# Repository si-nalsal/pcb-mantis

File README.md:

# SvayamV3_IIK — STM32H743 Flight Controller

**6-layer · 125 × 90 mm · STM32H743IIK6 · 16 servo channels · 9 protected peripheral ports**

> ### ⚠️ Design status: layout in progress — **not fabrication-ready**
> Schematic is complete and frozen (ERC **0 errors**). Placement is finalised and **every
> functional net is electrically connected** (`unconnected_items` = 0), but DRC still reports
> **2 shorts** — both vias sitting inside one unassigned connector `MP` pad — plus vias and
> drills outside the current rule set. **Do not order boards from this revision.**
> See [docs/STATUS.md](docs/STATUS.md).

---

## Contents

| | |
|---|---|
| [What this is](#what-this-is) | [Board specifications](#board-specifications) |
| [Hardware architecture](#hardware-architecture) | [Repository layout](#repository-layout) |
| [Documentation](#documentation) | [Opening the project](#opening-the-project) |
| [Board statistics](#board-statistics) | [Fabrication](#fabrication) |
| [Open items before fabrication](#open-items-before-fabrication) | [License](#license) |

---

## What this is

A servo-based UAV flight controller built around the **STM32H743IIK6** (Cortex-M7,
UFBGA-201, 0.65 mm pitch). The board distributes power to a fixed-wing/multirotor airframe
with **16 PWM servo outputs**, redundant IMU and barometer sensing, dual CAN, USB-C, micro-SD
logging, and nine current-limited peripheral ports for GPS, telemetry radios, and external
sensors.

Design priorities, in order:

1. **Repairability** — silkscreen carries *function* labels (`Channel 1`…`Channel 16`,
   `TELEM1`, `GPS`, `SBUS`, …) instead of values; component values live on the `F.Fab`
   layer so they stay readable in the editor and in fab documentation without cluttering
   the assembled board.
2. **Survivability** — every external port sits behind a TPS2553 current limiter; TVS
   diodes on the battery and servo rails; separate LDO domains for FMU and sensors.
3. **Do-no-harm to the airframe** — the `+VSERVO` rail is *fail-last*: it has no on-board
   source and no series fuse, so a failed BEC cannot brown out the flight controller.

---

## Board specifications

| Parameter | Value | Source |
|---|---|---|
| Board size | 125.15 × 89.96 mm (11,258 mm²) | `kicad-cli pcb export stats` |
| Layers | 6 — `F.Cu` / `In1.Cu` / `In2.Cu` / `In3.Cu` / `In4.Cu` / `B.Cu` | board setup |
| Finished thickness | 1.5584 mm | board setup |
| Copper weight | 1 oz outer (35 µm), 0.5 oz inner (15.2 µm) | board setup |
| Target stackup | JLCPCB `JLC06161H-3313` (3313 / FR4 / 2116 prepregs) | [docs/STACKUP.md](docs/STACKUP.md) |
| Surface finish | ENIG | board setup |
| MCU | STM32H743IIK6 — UFBGA-201, 10 × 10 mm, 0.65 mm pitch | `U1` |
| HSE crystal | 8 MHz, SMD5032-2P | `Y1` (X50328MSB2GI) |
| Minimum track width | 0.10 mm (BGA fan-out only) | DRC report |
| Minimum drill | 0.15 mm (BGA fan-out vias) | DRC report |
| Vias | 475 through-hole (0.30 / 0.20 / 0.15 mm drill) | board stats |
| Pads | 1,005 SMD · 63 THT · 6 NPTH | board stats |
| Component placements | 290 (190 front / 100 back) | board stats |
| Design rules | `SvayamV3_IIK.kicad_dru` — global 0.127 mm, BGA rule area, net classes | project |

---

## Hardware architecture

### Compute and storage

| Ref | Part | Function |
|---|---|---|
| `U1` | STM32H743IIK6 | Cortex-M7 FMU, 480 MHz |
| `U2` | FM25CL64B | 64 kbit FRAM for parameters (SPI) |
| `J10` | Molex 104031-0811 | micro-SD card, card-detect |
| `J7` | 1×05 2.54 mm | SWD / debug service header |
| `Y1` | X50328MSB2GI | 8 MHz HSE crystal (`U1` PH0/PH1) |

### Sensing — redundant by design

| Ref | Part | Function |
|---|---|---|
| `U7` | BMI088 | IMU #1 (accel + gyro) |
| `U8` | BMI270 | IMU #2 |
| `U5` | BMP388 | barometer #1 |
| `U6` | DPS310XTSA1 | barometer #2 |
| `U9` | BMM150 | magnetometer (WLCSP-12) |

The sensor block is laid out as its own quiet zone with a dedicated `+3V3_SENS` domain and
local copper pour, kept away from the switching regulator.

### Power chain

```
POWER1 (J9) ─┐
             ├─► U10 TPS2120  power mux ─► U11 TPS63070  buck-boost 5 V ─► U14 AP22804 ─► +5V_PERIPH
POWER2 (J16)─┘        (ILIM R24 = 33k)          (R27/R28 → 4.99 V)                        │
                                                                                          ├─► U16…U24  9× TPS2553 current limiters
                                                                                          │     GPS · TELEM1 · TELEM2 · SERIAL4 ·
                                                                                          │     SERIAL5 · I2C · CAN · CAN2 · SPI
                                              U12 RT9080 ─► +3V3_FMU  (MCU, IO)            │
                                              U13 RT9080 ─► +3V3_SENS (sensor zone)        │
                                              U15 USBLC6-2SC6 ─► USB-C ESD              +VSERVO
                                                                                          (external BEC, fail-last)
```

* TVS: `D4`/`D5` on `+VBRICK1`/`+VBRICK2`, `D8` SMAJ6.0A on `+VSERVO`.
* `+VSERVO` reservoir: `C78` 220 µF bulk + 16 × 1 µF per channel.
* Per-port trip current is set by each limiter's `RILIM`: `U16` R84 33k, `U17` R85 33k,
  `U18` R86 75k, `U19` R87 75k, `U20` R88 110k, `U21` R89 47k, `U22` R90 56k,
  `U23` R91 110k, `U24` R92 47k.

### Connectors

| Purpose | Ref | Purpose | Ref |
|---|---|---|---|
| POWER1 | `J9` | POWER2 | `J16` |
| RCIN / SBUS | `J6` | GPS | `J2` |
| TELEM1 | `J4` | TELEM2 | `J5` |
| SERIAL4 | `J8` | SERIAL5 | `J14` |
| I2C | `J17` | SPI | `J3` |
| CAN | `J13` | CAN2 | `J18` |
| SAFETY | `J15` | BUZZER | `J11` |
| ADC | `J12` | SD card | `J10` |
| USB-C | `J1` | SWD service | `J7` |

Servo outputs `J19`–`J34` (JST-XH `B3B-XH-A`, 2.50 mm, pin order **S / V+ / GND**) map
`Channel 1`…`Channel 16` in physical order along the board edge.

---

## Repository layout

```
.
├── SvayamV3_IIK.kicad_pro      # KiCad 10 project
├── SvayamV3_IIK.kicad_sch      # root sheet
│   ├── microcontroller.kicad_sch
│   ├── sensor.kicad_sch
│   ├── power.kicad_sch
│   └── connector.kicad_sch
├── SvayamV3_IIK.kicad_pcb      # 6-layer board
├── SvayamV3_IIK.kicad_dru      # custom DRC rules (global + BGA rule area)
├── fp-lib-table                # project footprint table (${KIPRJMOD})
├── sym-lib-table               # project symbol table (${KIPRJMOD})
├── Library/                    # custom + converted libraries (symbols, footprints, 3D)
├── docs/
│   ├── schematic.pdf           # full multi-sheet schematic (exported)
│   ├── STATUS.md               # live status + open DRC items
│   ├── DESIGN.md               # design decisions and their rationale
│   ├── STACKUP.md              # layer stackup and impedance notes
│   ├── board-stats.txt         # kicad-cli board statistics
│   ├── bom.csv                 # BOM (grouped by value + footprint)
│   ├── images/                 # PCB previews for this README
│   └── reports/                # dated ERC / DRC reports
└── fabrication/
    └── README.md               # fab gate, export commands, JLCPCB notes
```

Machine-local working files (`.history/`, `output/`, `*-backups/`, `*.kicad_prl`,
`.deepseek-sources/`) are deliberately **not** tracked — see `.gitignore`.

---

## Documentation

| Document | What it answers |
|---|---|
| [docs/STATUS.md](docs/STATUS.md) | Where the design is right now; open DRC items; next steps |
| [docs/DESIGN.md](docs/DESIGN.md) | Why the power chain, limiter setpoints and sensor redundancy look like this |
| [docs/STACKUP.md](docs/STACKUP.md) | Layer order, dielectrics, trace width / current table, via classes |
| [docs/schematic.pdf](docs/schematic.pdf) | Printable schematic, all four sheets |
| [docs/bom.csv](docs/bom.csv) | BOM — 88 line items (49 still need an MPN) |
| [docs/reports/](docs/reports/) | Raw `kicad-cli` ERC and DRC output, dated |
| [fabrication/README.md](fabrication/README.md) | What must pass before gerbers may be exported |

---

## Opening the project

1. KiCad **10.0** or newer (`generator_version 10.0`, format `20260206`). Older KiCad
   cannot open the project.
2. Open `SvayamV3_IIK.kicad_pro`. Both library tables resolve through `${KIPRJMOD}`, so the
   project is self-contained — no global library setup required.
3. Run **Tools → Update PCB from Schematic (F8)** only if the PCB and schematic have drifted;
   on a clean checkout they are in parity (0 issues).

> **Known limitation:** `sym-lib-table` registers the custom library under the nickname
> `Svayam_Symbol`, while the schematic references it as `Svayam`, and a stale `tps63070`
> entry points at a footprint directory. Symbols are embedded in the sheets, so the project
> opens and plots correctly — but ERC will report 9 `lib_symbol_issues` warnings until the
> table nickname is aligned. See [docs/STATUS.md](docs/STATUS.md#known-library-table-issues).

---

## Board statistics

Numbers below come straight from `kicad-cli pcb export stats` and the ERC/DRC reports in
[docs/reports/](docs/reports/):

| Metric | Value |
|---|---|
| Footprints | 290 (190 front, 100 back — 19 THT, 267 SMD, 4 mechanical) |
| Nets | 262 (203 carry copper, 59 are single-pin NC) |
| Nodes | 1,005 |
| Track segments | 2,897 |
| Vias | 475 through-hole |
| Copper zones | 8 |
| ERC | **0 errors / 17 warnings** (all library-symbol cosmetics) |
| DRC | 752 findings (313 error / 439 warning) — see below for the ones that matter |
| Schematic parity | 0 issues |

---

## Fabrication

**No gerbers are published for this revision — the design is not ready to order.**
The release gate and exact commands live in [fabrication/README.md](fabrication/README.md).

Intended process: **JLCPCB, 6 layers, 1.6 mm, ENIG**, stackup `JLC06161H-3313`.

---

## Open items before fabrication

| # | Item | Count | Notes |
|---|---|---|---|
| 1 | `shorting_items` | 2 | both are `+5V_PERIPH` vias inside the left `MP` pad of `J17` — not a live short while `MP` is unassigned, but **move them before** tying `MP` to GND |
| 2 | ~~`unconnected_items`~~ | ~~7~~ → **0** | closed 2026-10-25: `R1`/`J9`/`C24` GND, `U1` pad `K4` (an MCU `VDD` pin), `+VBRICK1/2`, `SPI1_MISO` |
| 3 | `drill_out_of_range` | 6 | 0.15 mm fan-out vias vs 0.20 mm rule floor — confirm fab tier before ordering |
| 4 | `track_width` | 199 | 0.10 mm tracks **outside** the `U1_BGA` rule area (151 `F.Cu`, 48 `B.Cu`) — enlarge the rule area or raise the global minimum |
| 5 | `clearance` / `hole_clearance` | 27 / 24 | BGA fan-out, 0.10–0.12 mm actual vs 0.12–0.33 mm rule |
| 6 | `courtyards_overlap` | 7 | `R84`–`R92` sit inside their connector courtyards |
| 7 | `silk_overlap` / `silk_over_copper` | 199 / 55 | Cosmetic; clean up with Autoplace Fields at the end |
| 8 | `lib_footprint_mismatch` | 119 | Footprint cache drift, not a geometry error |
| 9 | BOM sourcing | 49 / 88 | Line items without an MPN; LCSC field still empty |
| 10 | Mounting holes | 4 | `H1`–`H4` still parked outside the board outline at X = 223.78 mm |

Full detail: [docs/reports/drc-2026-10-25.txt](docs/reports/drc-2026-10-25.txt).

---

## Design references

* **[PCB Design Tutorial, Rev. A — David L. Jones](https://www.alternatezone.com/electronics/files/PCBDesignTutorialRevA.pdf)** —
  track width / current tables, copper pour practice, silkscreen conventions.
* **IPC-2221** — conductor spacing and current capacity.
* **JST XH series datasheet** — 3 A per contact (AWG22) limit used to size the servo stubs.
* Component datasheets: STM32H743II, TPS63070, TPS2120, TPS2553-Q1, AP22804, RT9080,
  BMI088, BMI270, BMP388, DPS310, BMM150, FM25CL64B, TJA1051.

---

## License

Hardware design files are released under **CERN-OHL-S-2.0** — see [LICENSE](LICENSE).
You may study, modify, manufacture and distribute the design, provided derivative hardware
is released under the same licence.

---

## Credits

Designed and routed in **KiCad 10.0**. Schematic symbols and footprints for the custom
sensors and connectors were converted with **easyeda2kicad** and vendored into `Library/`.

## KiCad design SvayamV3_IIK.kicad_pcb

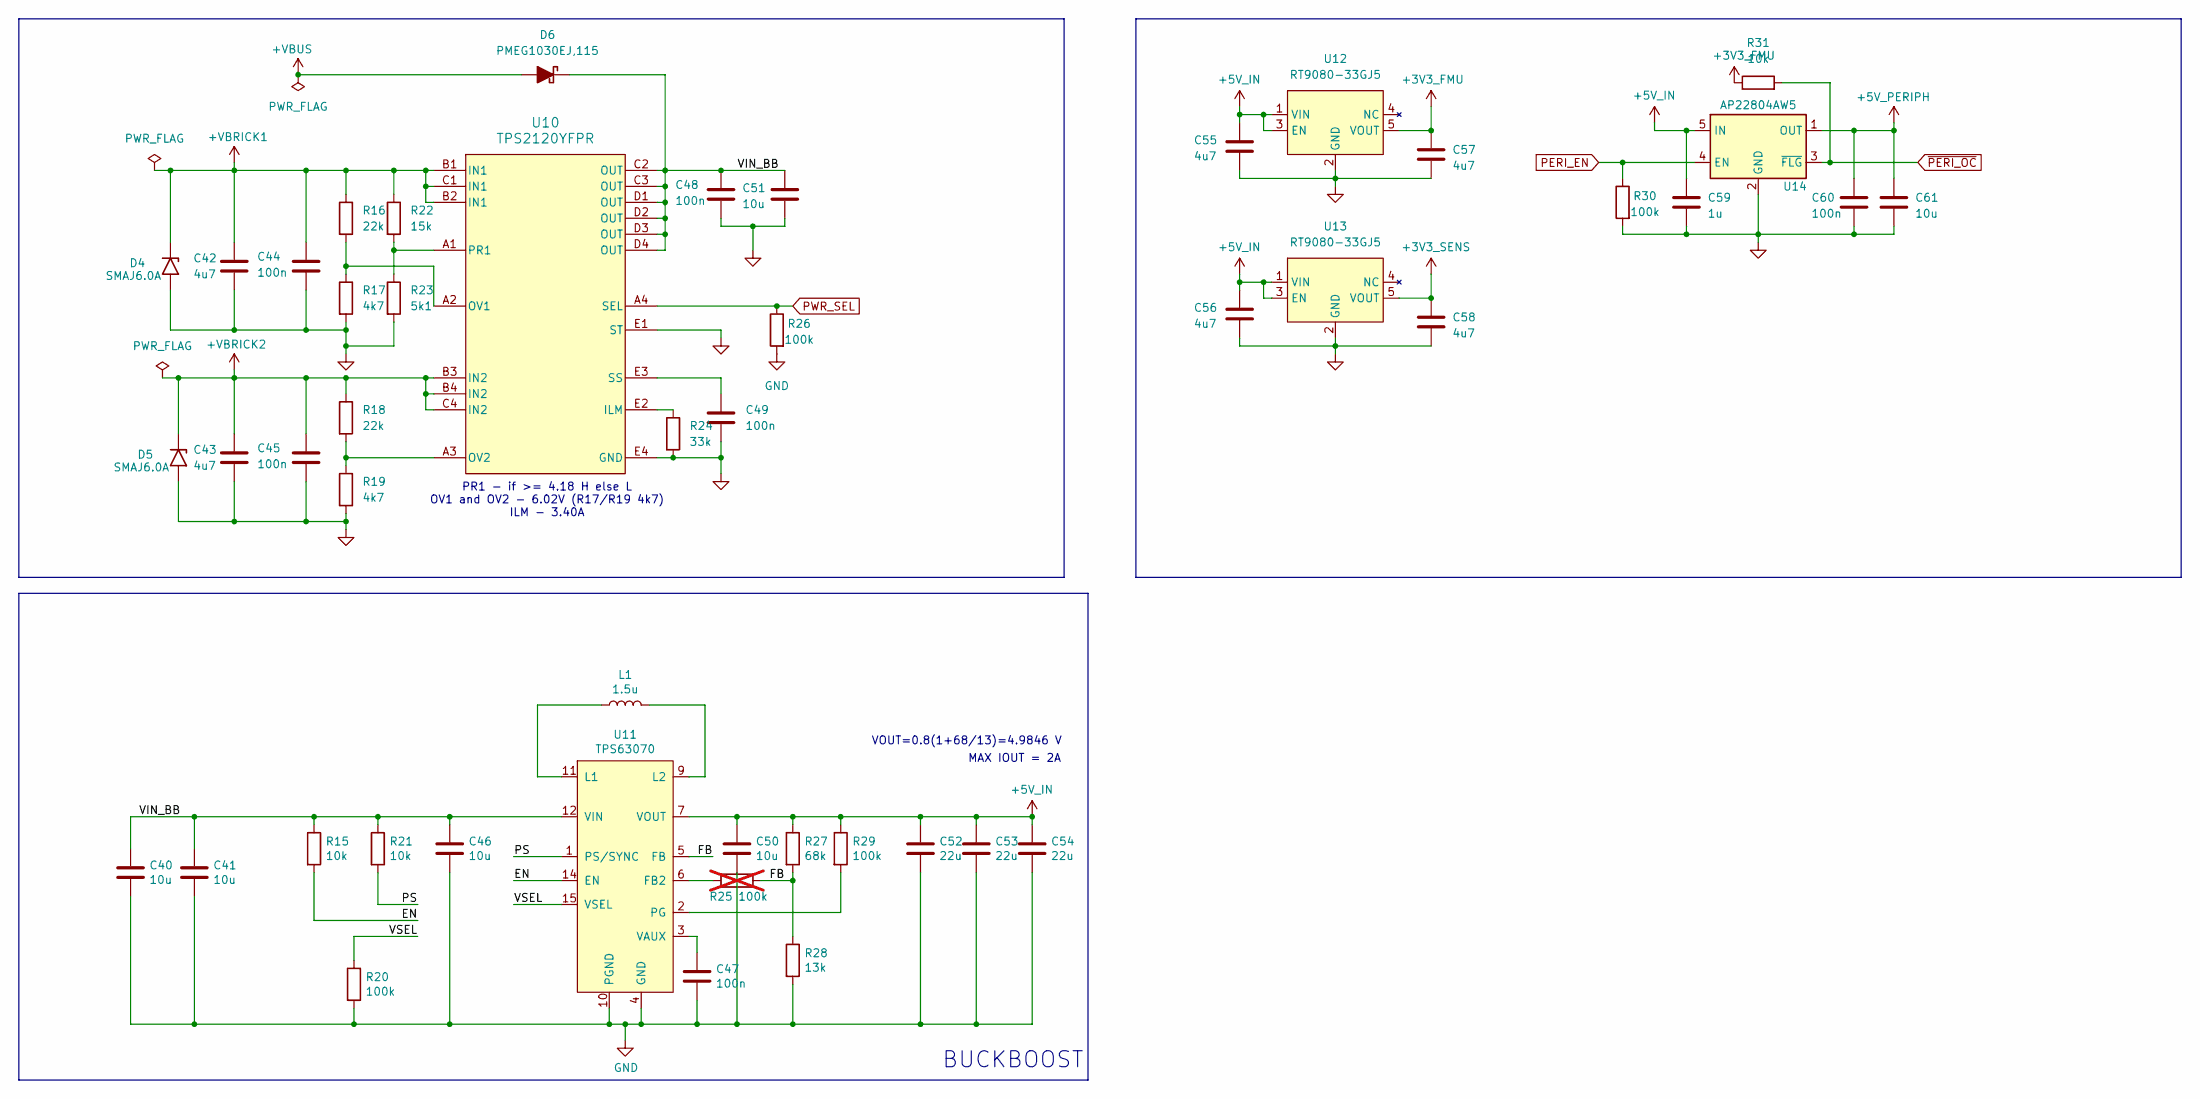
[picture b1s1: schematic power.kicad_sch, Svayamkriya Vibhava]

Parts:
C40, C41: 10u; C_0805_2012Metric; MPN CL21A106KAYNNNE; LCSC C15850
C42, C43, C55, C56, C57, C58: 4u7; C_0603_1608Metric; MPN CL10A475KO8NNNC; LCSC C19666
C44, C45, C48, C49, C60: 100n; C_0402_1005Metric; MPN CL05B104KB54PNC; LCSC C307331
C46, C50, C51, C61: 10u; C_0603_1608Metric; MPN CL10A106MA8NRNC; LCSC C96446
C47: 100n; C_0805_2012Metric; MPN CC0805KRX7R9BB104; LCSC C49678
C52, C53, C54: 22u; C_0805_2012Metric; MPN CL21A226MAQNNNE; LCSC C45783
C59: 1u; C_0603_1608Metric; MPN CL10A105KB8NNNC; LCSC C15849
D4, D5: SMAJ6.0A; D_SMA; MPN SMAJ6.0A; LCSC C353434
D6: PMEG1030EJ,115; D_SOD-323F; MPN PMEG1030EJ,115; LCSC C133633
L1: 1.5u; L_Coilcraft_XxL4020; MPN XGL4020-152MEC; LCSC C7417180
R15, R21: 10k; R_0805_2012Metric; MPN 0805W8F1002T5E; LCSC C17414
R16, R18: 22k; R_0402_1005Metric; MPN 0402WGF2202TCE; LCSC C25768
R17, R19: 4k7; R_0402_1005Metric; MPN 0402WGF4701TCE; LCSC C25900
R20, R29: 100k; R_0805_2012Metric; MPN 0805W8F1003T5E; LCSC C149504
R22: 15k; R_0402_1005Metric; MPN 0402WGF1502TCE; LCSC C25756
R23: 5k1; R_0402_1005Metric; MPN 0402WGF5101TCE; LCSC C25905
R24: 33k; R_0402_1005Metric; MPN 0402WGF3302TCE; LCSC C25779
R25: 100k; R_0805_2012Metric; MPN 0805W8F1003T5E; LCSC C149504; not fitted
R26, R30: 100k; R_0402_1005Metric; MPN 0402WGF1003TCE; LCSC C25741
R27: 68k; R_0805_2012Metric; MPN 0805W8F6802T5E; LCSC C17801
R28: 13k; R_0805_2012Metric; MPN 0805W8F1302T5E; LCSC C17455
R31: 10k; R_0402_1005Metric; MPN 0402WGF1002TCE; LCSC C25744
U10: TPS2120YFPR; Texas_YFP0020_DSBGA-20_1.588x1.988mm_Layout4x5_P0.4mm; MPN TPS2120YFPR; LCSC C1850326
U11: TPS63070; VQFN-HR-15; MPN TPS63070RNMR; LCSC C109322
U12, U13: RT9080-33GJ5; TSOT-23-5; MPN RT9080-33GJ5; LCSC C841192
U14: AP22804AW5; SOT-23-5; MPN AP22804AW5-7; LCSC C3001659

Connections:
+3V3_FMU: C57.1, R31.1, U12.5 (VOUT); also elsewhere on the board
+3V3_SENS: C58.1, U13.5 (VOUT); also elsewhere on the board
+5V_IN: C50.1, C52.1, C53.1, C54.1, C55.1, C56.1, C59.1, R27.1, R29.1, U11.7 (VOUT), U12.1 (VIN), U12.3 (EN), U13.1 (VIN), U13.3 (EN), U14.5 (IN); also elsewhere on the board
+5V_PERIPH: C60.1, C61.1, U14.1 (OUT); also elsewhere on the board
+VBRICK1: C42.1, C44.1, D4.1 (A1), R16.1, R22.1, U10.B1 (IN1), U10.B2 (IN1), U10.C1 (IN1); also elsewhere on the board
+VBRICK2: C43.1, C45.1, D5.1 (A1), R18.1, U10.B3 (IN2), U10.B4 (IN2), U10.C4 (IN2); also elsewhere on the board
+VBUS: D6.2 (A); also elsewhere on the board
/Power/EN: R15.2, U11.14 (EN)
/Power/FB: R25.1, R27.2, R28.1, U11.5 (FB)
/Power/PS: R21.2, U11.1 (PS/SYNC)
/Power/VIN_BB: C40.1, C41.1, C46.1, C48.1, C51.1, D6.1 (K), R15.1, R21.1, U10.C2 (OUT), U10.C3 (OUT), U10.D1 (OUT), U10.D2 (OUT), U10.D3 (OUT), U10.D4 (OUT), U11.12 (VIN)
/Power/VSEL: R20.1, U11.15 (VSEL)
GND: C40.2, C41.2, C42.2, C43.2, C44.2, C45.2, C46.2, C47.1, C48.2, C49.2, C50.2, C51.2, C52.2, C53.2, C54.2, C55.2, C56.2, C57.2, C58.2, C59.2, C60.2, C61.2, D4.2 (A2), D5.2 (A2), R17.2, R19.2, R20.2, R23.2, R24.2, R26.2, R28.2, R30.2, U10.E1 (ST), U10.E4 (GND), U11.4 (GND), U11.10 (PGND), U12.2 (GND), U13.2 (GND), U14.2 (GND); also elsewhere on the board
unnamed: R24.1, U10.E2 (ILM)
unnamed: R16.2, R17.1, U10.A2 (OV1)
unnamed: R18.2, R19.1, U10.A3 (OV2)
unnamed: R22.2, R23.1, U10.A1 (PR1)
unnamed: C49.1, U10.E3 (SS)
unnamed: R25.2, U11.6 (FB2)
unnamed: L1.1, U11.11 (L1)
unnamed: L1.2, U11.9 (L2)
unnamed: R29.2, U11.2 (PG)
unnamed: C47.2, U11.3 (VAUX)
PERI_EN: R30.1, U14.4 (EN); also elsewhere on the board
PWR_SEL: R26.1, U10.A4 (SEL); also elsewhere on the board
~PERI_OC: R31.2, U14.3 (~FLG); also elsewhere on the board

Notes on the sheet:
MAX IOUT = 2A
BUCKBOOST
PR1 - if >= 4.18 H else L OV1 and OV2 - 6.02V (R17/R19 4k7) ILM - 3.40A
VOUT​=0.8(1+68/13)=4.9846 V​

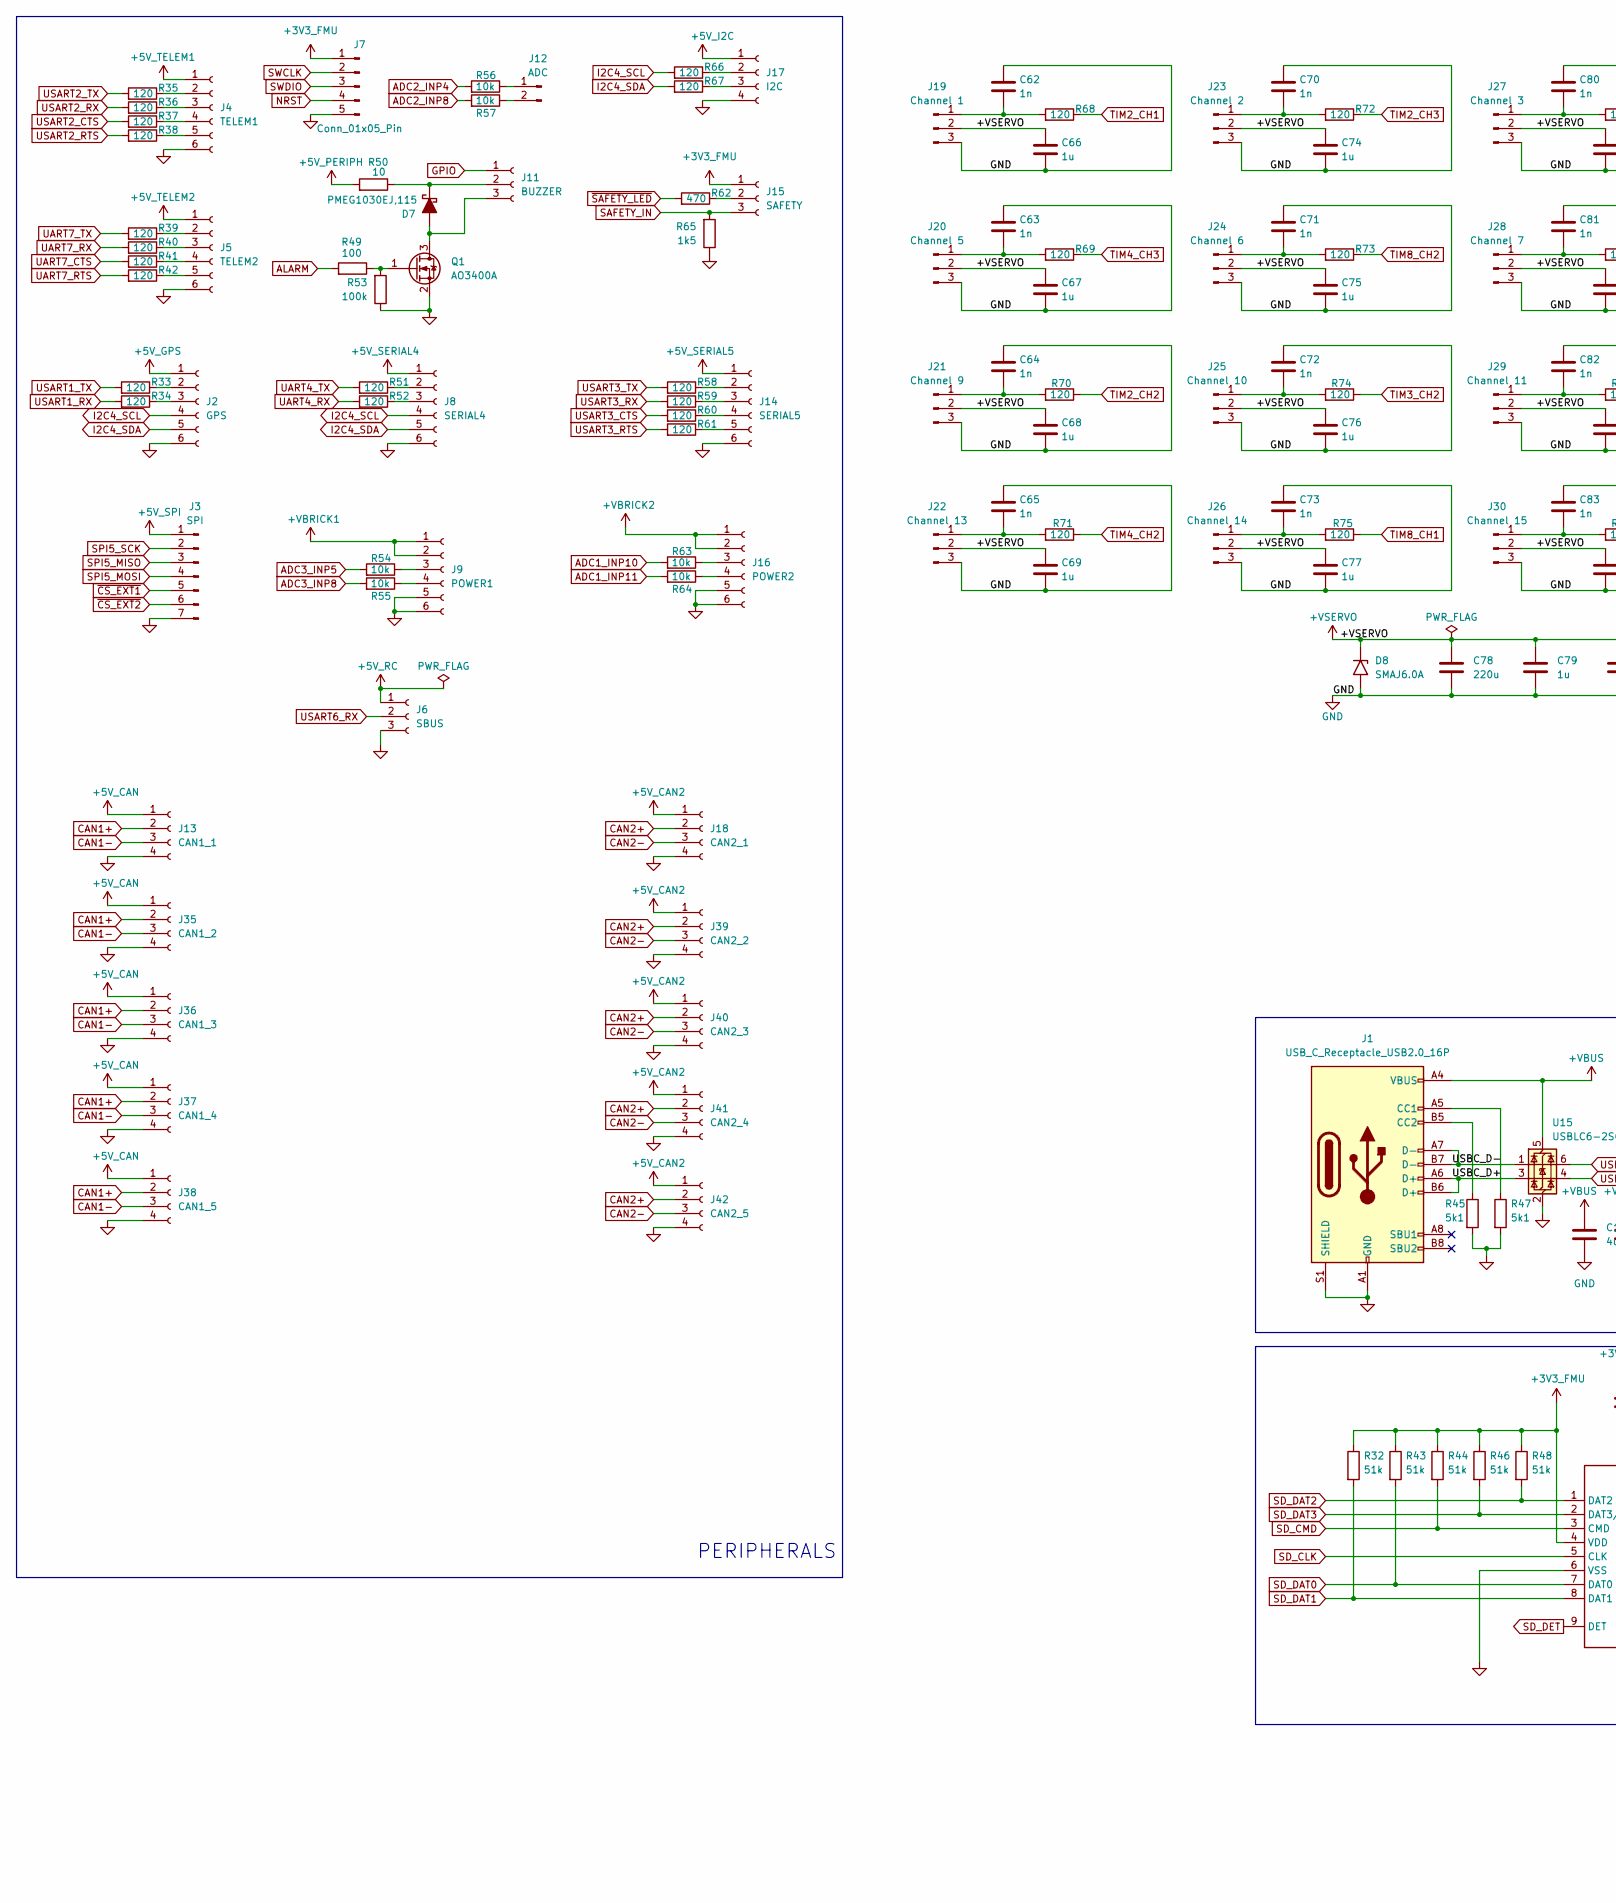
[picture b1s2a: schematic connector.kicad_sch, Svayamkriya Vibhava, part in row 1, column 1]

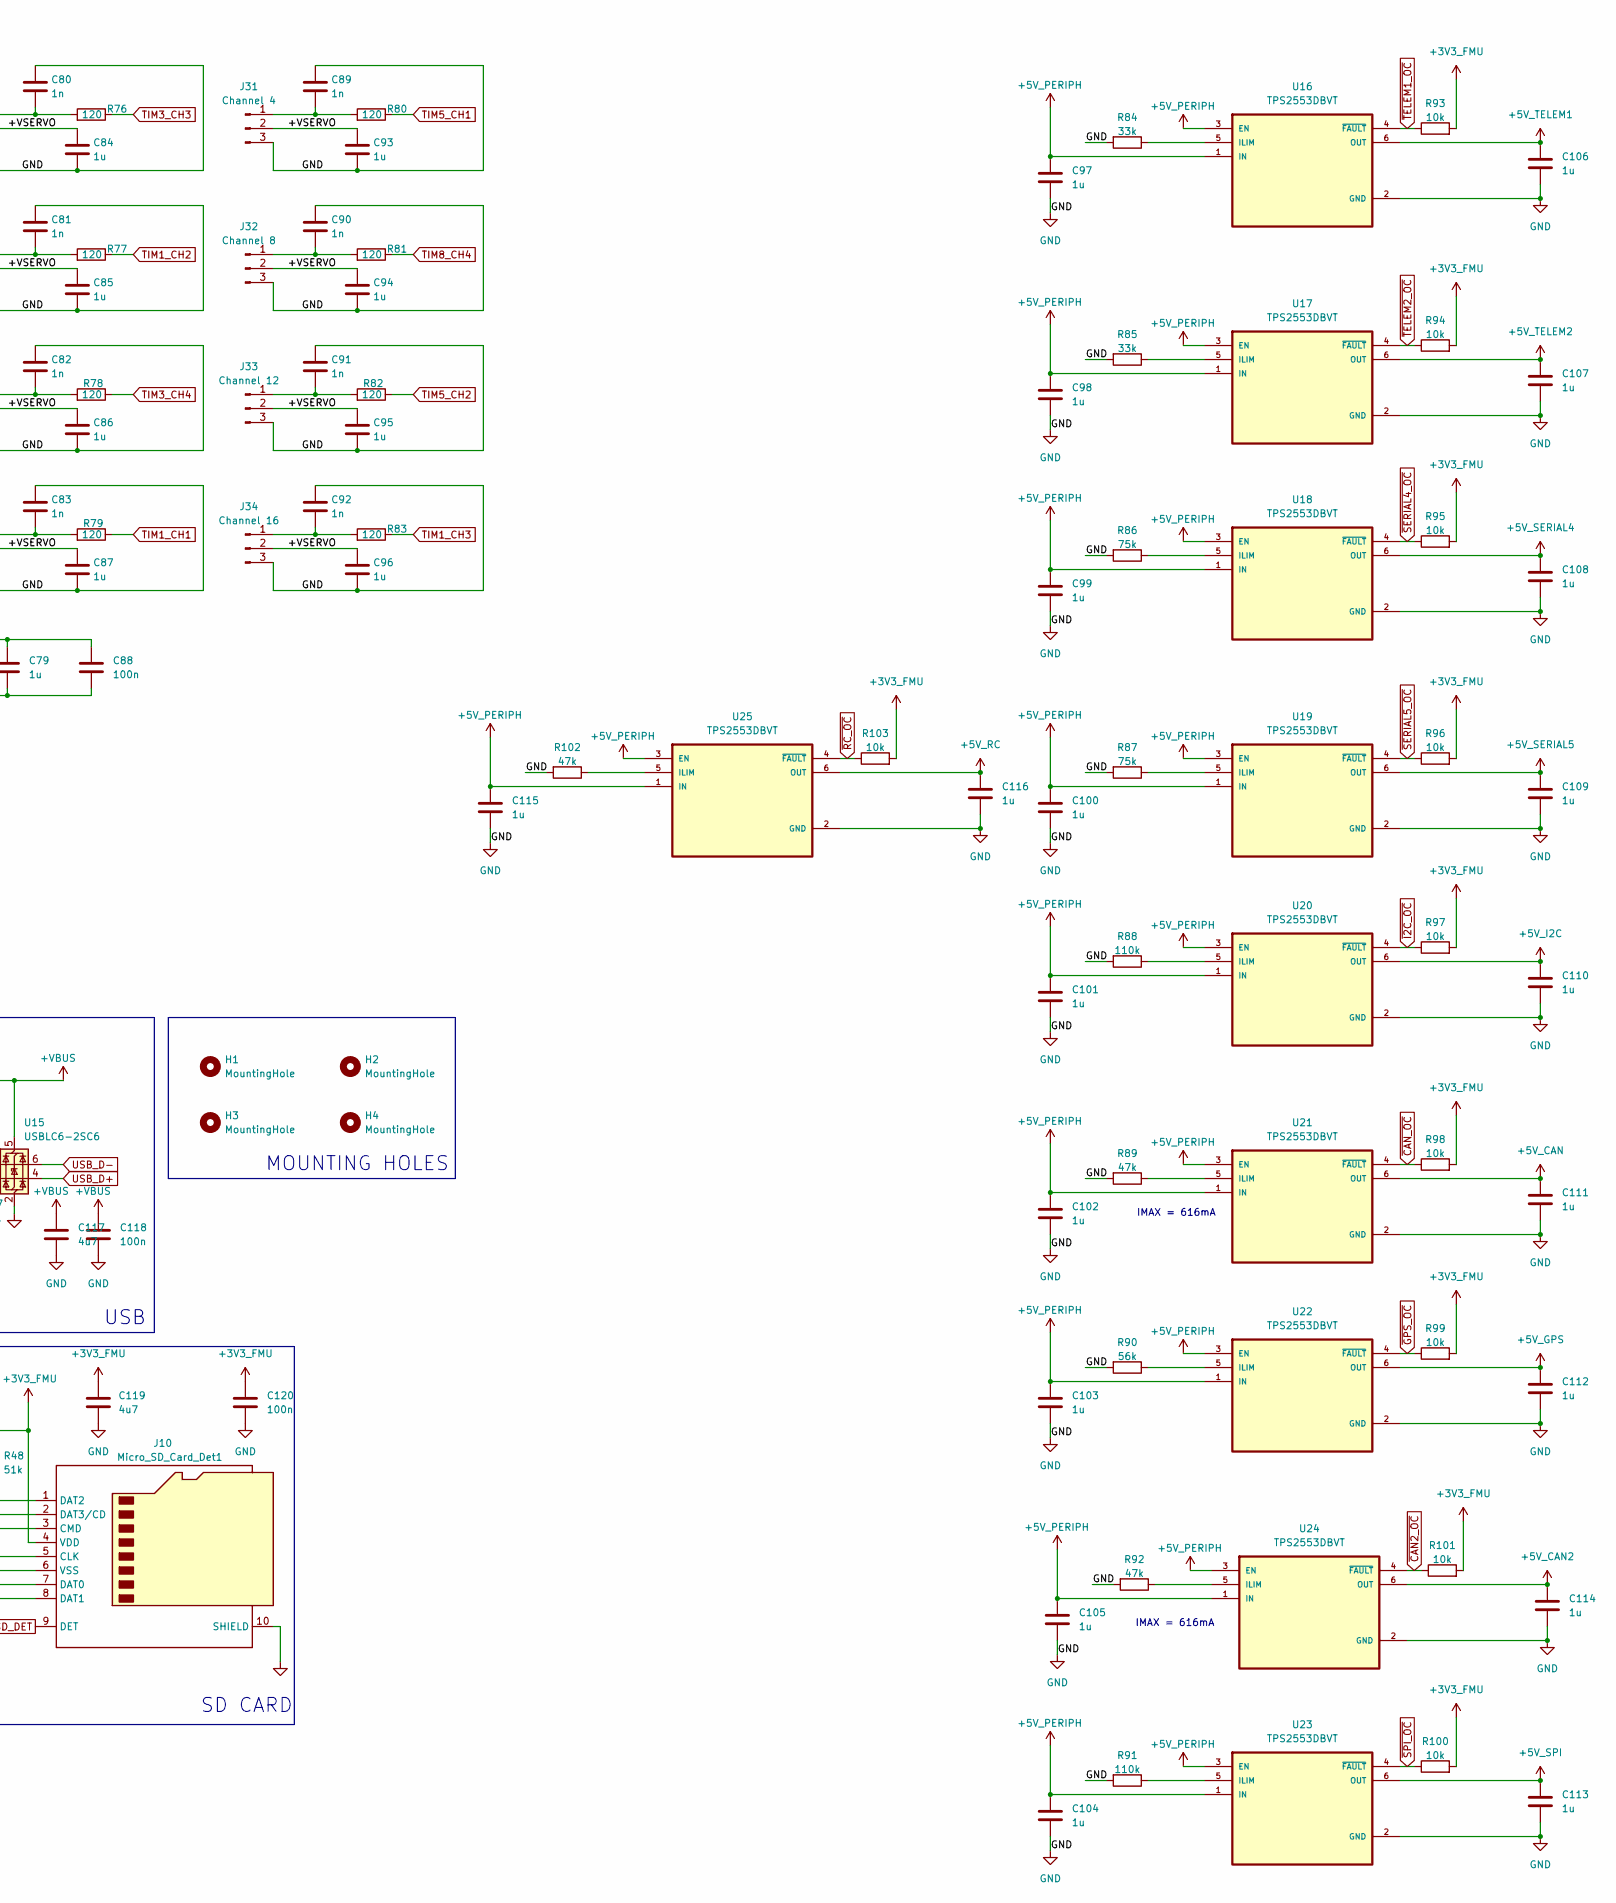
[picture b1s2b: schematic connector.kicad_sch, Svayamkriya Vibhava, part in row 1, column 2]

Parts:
C62, C63, C64, C65, C70, C71, C72, C73, C80, C81, C82, C83, C89, C90, C91, C92: 1n; C_0402_1005Metric; MPN 0402B102K500NT; LCSC C1523
C66, C67, C68, C69, C74, C75, C76, C77, C79, C84, C85, C86, C87, C93, C94, C95, C96, C97, C98, C99, C100, C101, C102, C103, C104, C105, C106, C107, C108, C109, C110, C111, C112, C113, C114, C115, C116: 1u; C_0603_1608Metric; MPN CL10A105KB8NNNC; LCSC C15849
C78: 220u; CP_Elec_6.3x7.7; MPN VT1C221M0607; LCSC C90274
C88, C118, C120: 100n; C_0402_1005Metric; MPN CL05B104KB54PNC; LCSC C307331
C117, C119: 4u7; C_0603_1608Metric; MPN CL10A475KO8NNNC; LCSC C19666
D7: PMEG1030EJ,115; D_SOD-323F; MPN PMEG1030EJ,115; LCSC C133633
D8: SMAJ6.0A; D_SMA; MPN SMAJ6.0A; LCSC C353434
H1, H2, H3, H4: MountingHole; MountingHole_3.2mm_M3
J1: USB_C_Receptacle_USB2.0_16P; USB-C-SMD_TYPE-C16PIN; MPN TYPE-C16PIN; LCSC C393939
J2: GPS; JST_GH_BM06B-GHS-TBT_1x06-1MP_P1.25mm_Vertical; MPN BM06B-GHS-TBT(LF)(SN); LCSC C189892
J3: SPI; JST_GH_BM07B-GHS-TBT_1x07-1MP_P1.25mm_Vertical; MPN BM07B-GHS-TBT(LF)(SN)(N); LCSC C378970
J4: TELEM1; JST_GH_BM06B-GHS-TBT_1x06-1MP_P1.25mm_Vertical; MPN BM06B-GHS-TBT(LF)(SN); LCSC C189892
J5: TELEM2; JST_GH_BM06B-GHS-TBT_1x06-1MP_P1.25mm_Vertical; MPN BM06B-GHS-TBT(LF)(SN); LCSC C189892
J6: SBUS; JST_GH_BM03B-GHS-TBT_1x03-1MP_P1.25mm_Vertical; MPN BM03B-GHS-TBT(LF)(SN); LCSC C161691
J7: Conn_01x05_Pin; PinHeader_1x05_P2.54mm_Vertical; MPN PZ254V-11-05P; LCSC C492404
J8: SERIAL4; JST_GH_BM06B-GHS-TBT_1x06-1MP_P1.25mm_Vertical; MPN BM06B-GHS-TBT(LF)(SN); LCSC C189892
J9: POWER1; JST_GH_BM06B-GHS-TBT_1x06-1MP_P1.25mm_Vertical; MPN BM06B-GHS-TBT(LF)(SN); LCSC C189892
J10: Micro_SD_Card_Det1; 104031-0811_MOL; MPN 1040310811; LCSC C585350
J11: BUZZER; JST_GH_BM03B-GHS-TBT_1x03-1MP_P1.25mm_Vertical; MPN BM03B-GHS-TBT(LF)(SN); LCSC C161691
J12: ADC; PinHeader_1x02_P2.54mm_Vertical; MPN PZ254V-11-02P; LCSC C492401
J13: CAN1_1; JST_GH_BM04B-GHS-TBT_1x04-1MP_P1.25mm_Vertical; MPN BM04B-GHS-TBT(LF)(SN); LCSC C161692
J14: SERIAL5; JST_GH_BM06B-GHS-TBT_1x06-1MP_P1.25mm_Vertical; MPN BM06B-GHS-TBT(LF)(SN); LCSC C189892
J15: SAFETY; JST_GH_BM03B-GHS-TBT_1x03-1MP_P1.25mm_Vertical; MPN BM03B-GHS-TBT(LF)(SN); LCSC C161691
J16: POWER2; JST_GH_BM06B-GHS-TBT_1x06-1MP_P1.25mm_Vertical; MPN BM06B-GHS-TBT(LF)(SN); LCSC C189892
J17: I2C; JST_GH_BM04B-GHS-TBT_1x04-1MP_P1.25mm_Vertical; MPN BM04B-GHS-TBT(LF)(SN); LCSC C161692
J18: CAN2_1; JST_GH_BM04B-GHS-TBT_1x04-1MP_P1.25mm_Vertical; MPN BM04B-GHS-TBT(LF)(SN); LCSC C161692
J19: Channel 1; JST_XH_B3B-XH-A_1x03_P2.50mm_Vertical; MPN B3B-XH-A(LF)(SN); LCSC C144394
J20: Channel 5; JST_XH_B3B-XH-A_1x03_P2.50mm_Vertical; MPN B3B-XH-A(LF)(SN); LCSC C144394
J21: Channel 9; JST_XH_B3B-XH-A_1x03_P2.50mm_Vertical; MPN B3B-XH-A(LF)(SN); LCSC C144394
J22: Channel 13; JST_XH_B3B-XH-A_1x03_P2.50mm_Vertical; MPN B3B-XH-A(LF)(SN); LCSC C144394
J23: Channel 2; JST_XH_B3B-XH-A_1x03_P2.50mm_Vertical; MPN B3B-XH-A(LF)(SN); LCSC C144394
J24: Channel 6; JST_XH_B3B-XH-A_1x03_P2.50mm_Vertical; MPN B3B-XH-A(LF)(SN); LCSC C144394
J25: Channel 10; JST_XH_B3B-XH-A_1x03_P2.50mm_Vertical; MPN B3B-XH-A(LF)(SN); LCSC C144394
J26: Channel 14; JST_XH_B3B-XH-A_1x03_P2.50mm_Vertical; MPN B3B-XH-A(LF)(SN); LCSC C144394
J27: Channel 3; JST_XH_B3B-XH-A_1x03_P2.50mm_Vertical; MPN B3B-XH-A(LF)(SN); LCSC C144394
J28: Channel 7; JST_XH_B3B-XH-A_1x03_P2.50mm_Vertical; MPN B3B-XH-A(LF)(SN); LCSC C144394
J29: Channel 11; JST_XH_B3B-XH-A_1x03_P2.50mm_Vertical; MPN B3B-XH-A(LF)(SN); LCSC C144394
J30: Channel 15; JST_XH_B3B-XH-A_1x03_P2.50mm_Vertical; MPN B3B-XH-A(LF)(SN); LCSC C144394
J31: Channel 4; JST_XH_B3B-XH-A_1x03_P2.50mm_Vertical; MPN B3B-XH-A(LF)(SN); LCSC C144394
J32: Channel 8; JST_XH_B3B-XH-A_1x03_P2.50mm_Vertical; MPN B3B-XH-A(LF)(SN); LCSC C144394
J33: Channel 12; JST_XH_B3B-XH-A_1x03_P2.50mm_Vertical; MPN B3B-XH-A(LF)(SN); LCSC C144394
J34: Channel 16; JST_XH_B3B-XH-A_1x03_P2.50mm_Vertical; MPN B3B-XH-A(LF)(SN); LCSC C144394
J35: CAN1_2; JST_GH_BM04B-GHS-TBT_1x04-1MP_P1.25mm_Vertical; MPN BM04B-GHS-TBT(LF)(SN); LCSC C161692
J36: CAN1_3; JST_GH_BM04B-GHS-TBT_1x04-1MP_P1.25mm_Vertical; MPN BM04B-GHS-TBT(LF)(SN); LCSC C161692
J37: CAN1_4; JST_GH_BM04B-GHS-TBT_1x04-1MP_P1.25mm_Vertical; MPN BM04B-GHS-TBT(LF)(SN); LCSC C161692
J38: CAN1_5; JST_GH_BM04B-GHS-TBT_1x04-1MP_P1.25mm_Vertical; MPN BM04B-GHS-TBT(LF)(SN); LCSC C161692
J39: CAN2_2; JST_GH_BM04B-GHS-TBT_1x04-1MP_P1.25mm_Vertical; MPN BM04B-GHS-TBT(LF)(SN); LCSC C161692
J40: CAN2_3; JST_GH_BM04B-GHS-TBT_1x04-1MP_P1.25mm_Vertical; MPN BM04B-GHS-TBT(LF)(SN); LCSC C161692
J41: CAN2_4; JST_GH_BM04B-GHS-TBT_1x04-1MP_P1.25mm_Vertical; MPN BM04B-GHS-TBT(LF)(SN); LCSC C161692
J42: CAN2_5; JST_GH_BM04B-GHS-TBT_1x04-1MP_P1.25mm_Vertical; MPN BM04B-GHS-TBT(LF)(SN); LCSC C161692
Q1: AO3400A; SOT-23; MPN AO3400A; LCSC C20917
R32, R43, R44, R46, R48: 51k; R_0402_1005Metric; MPN 0402WGF5102TCE; LCSC C25794
R33, R34, R35, R36, R37, R38, R39, R40, R41, R42, R51, R52, R58, R59, R60, R61, R66, R67, R68, R69, R70, R71, R72, R73, R74, R75, R76, R77, R78, R79, R80, R81, R82, R83: 120; R_0402_1005Metric; MPN 0402WGF1200TCE; LCSC C25079
R45, R47: 5k1; R_0402_1005Metric; MPN 0402WGF5101TCE; LCSC C25905
R49: 100; R_0402_1005Metric; MPN 0402WGF1000TCE; LCSC C25076
R50: 10; R_0402_1005Metric; MPN 0402WGF100JTCE; LCSC C25077
R53: 100k; R_0402_1005Metric; MPN 0402WGF1003TCE; LCSC C25741
R54, R55, R56, R57, R63, R64, R93, R94, R95, R96, R97, R98, R99, R100, R101, R103: 10k; R_0402_1005Metric; MPN 0402WGF1002TCE; LCSC C25744
R62: 470; R_0402_1005Metric; MPN 0402WGF4700TCE; LCSC C25117
R65: 1k5; R_0402_1005Metric; MPN 0402WGF1501TCE; LCSC C25867
R84, R85: 33k; R_0402_1005Metric; MPN 0402WGF3302TCE; LCSC C25779
R86, R87: 75k; R_0402_1005Metric; MPN 0402WGF7502TCE; LCSC C25798
R88, R91: 110k; R_0402_1005Metric; MPN 0402WGF1103TCE; LCSC C25745
R89, R92, R102: 47k; R_0402_1005Metric; MPN 0402WGF4702TCE; LCSC C25792
R90: 56k; R_0402_1005Metric; MPN 0402WGF5602TCE; LCSC C25796
U15: USBLC6-2SC6; SOT-23-6; MPN USBLC6-2SC6; LCSC C7519
U16, U17, U18, U19, U20, U21, U22, U23, U24, U25: TPS2553DBVT; SOT95P280X145-6N; MPN TPS2553DBVR; LCSC C55266

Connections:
+3V3_FMU: C119.1, C120.1, J7.1, J10.4 (VDD), J15.1, R32.1, R43.1, R44.1, R46.1, R48.1, R93.2, R94.2, R95.2, R96.2, R97.2, R98.2, R99.2, R100.2, R101.2, R103.2; also elsewhere on the board
+5V_CAN: C111.1, J13.1, J35.1, J36.1, J37.1, J38.1, U21.6 (OUT)
+5V_CAN2: C114.1, J18.1, J39.1, J40.1, J41.1, J42.1, U24.6 (OUT)
+5V_GPS: C112.1, J2.1, U22.6 (OUT)
+5V_I2C: C110.1, J17.1, U20.6 (OUT)
+5V_PERIPH: C97.1, C98.1, C99.1, C100.1, C101.1, C102.1, C103.1, C104.1, C105.1, C115.1, R50.2, U16.1 (IN), U16.3 (EN), U17.1 (IN), U17.3 (EN), U18.1 (IN), U18.3 (EN), U19.1 (IN), U19.3 (EN), U20.1 (IN), U20.3 (EN), U21.1 (IN), U21.3 (EN), U22.1 (IN), U22.3 (EN), U23.1 (IN), U23.3 (EN), U24.1 (IN), U24.3 (EN), U25.1 (IN), U25.3 (EN); also elsewhere on the board
+5V_RC: C116.1, J6.1, U25.6 (OUT)
+5V_SERIAL4: C108.1, J8.1, U18.6 (OUT)
+5V_SERIAL5: C109.1, J14.1, U19.6 (OUT)
+5V_SPI: C113.1, J3.1, U23.6 (OUT)
+5V_TELEM1: C106.1, J4.1, U16.6 (OUT)
+5V_TELEM2: C107.1, J5.1, U17.6 (OUT)
+VBRICK1: J9.1, J9.2; also elsewhere on the board
+VBRICK2: J16.1, J16.2; also elsewhere on the board
+VBUS: C117.1, C118.1, J1.A4 (VBUS), J1.A9 (VBUS), J1.B4 (VBUS), J1.B9 (VBUS), U15.5 (VBUS); also elsewhere on the board
+VSERVO: C66.1, C67.1, C68.1, C69.1, C74.1, C75.1, C76.1, C77.1, C78.1, C79.1, C84.1, C85.1, C86.1, C87.1, C88.1, C93.1, C94.1, C95.1, C96.1, D8.1 (A1), J19.2, J20.2, J21.2, J22.2, J23.2, J24.2, J25.2, J26.2, J27.2, J28.2, J29.2, J30.2, J31.2, J32.2, J33.2, J34.2
/Connector/USBC_D+: J1.A6 (D+), J1.B6 (D+), U15.3 (I/O2)
/Connector/USBC_D-: J1.A7 (D-), J1.B7 (D-), U15.1 (I/O1)
ADC1_INP10: R63.2; also elsewhere on the board
ADC1_INP11: R64.2; also elsewhere on the board
ADC2_INP4: R56.2; also elsewhere on the board
ADC2_INP8: R57.2; also elsewhere on the board
ADC3_INP5: R54.2; also elsewhere on the board
ADC3_INP8: R55.2; also elsewhere on the board
ALARM: R49.2; also elsewhere on the board
CAN1+: J13.2, J35.2, J36.2, J37.2, J38.2; also elsewhere on the board
CAN1-: J13.3, J35.3, J36.3, J37.3, J38.3; also elsewhere on the board
CAN2+: J18.2, J39.2, J40.2, J41.2, J42.2; also elsewhere on the board
CAN2-: J18.3, J39.3, J40.3, J41.3, J42.3; also elsewhere on the board
GND: C62.1, C63.1, C64.1, C65.1, C66.2, C67.2, C68.2, C69.2, C70.1, C71.1, C72.1, C73.1, C74.2, C75.2, C76.2, C77.2, C78.2, C79.2, C80.1, C81.1, C82.1, C83.1, C84.2, C85.2, C86.2, C87.2, C88.2, C89.1, C90.1, C91.1, C92.1, C93.2, C94.2, C95.2, C96.2, C97.2, C98.2, C99.2, C100.2, C101.2, C102.2, C103.2, C104.2, C105.2, C106.2, C107.2, C108.2, C109.2, C110.2, C111.2, C112.2, C113.2, C114.2, C115.2, C116.2, C117.2, C118.2, C119.2, C120.2, D8.2 (A2), J1.A1 (GND), J1.A12 (GND), J1.B1 (GND), J1.B12 (GND), J1.S1 (SHIELD), J2.6, J3.7, J4.6, J5.6, J6.3, J7.5, J8.6, J9.5, J9.6, J10.6 (VSS), J10.10 (SHIELD), J13.4, J14.6, J16.5, J16.6, J17.4, J18.4, J19.3, J20.3, J21.3, J22.3, J23.3, J24.3, J25.3, J26.3, J27.3, J28.3, J29.3, J30.3, J31.3, J32.3, J33.3, J34.3, J35.4, J36.4, J37.4, J38.4, J39.4, J40.4, J41.4, J42.4, Q1.2 (S), R45.2, R47.2, R53.1, R65.1, R84.2, R85.2, R86.2, R87.2, R88.2, R89.2, R90.2, R91.2, R92.2, R102.2, U15.2 (GND), U16.2 (GND), U17.2 (GND), U18.2 (GND), U19.2 (GND), U20.2 (GND), U21.2 (GND), U22.2 (GND), U23.2 (GND), U24.2 (GND), U25.2 (GND); also elsewhere on the board
GPIO: J11.1; also elsewhere on the board
I2C4_SCL: J2.4, J8.4, R66.2; also elsewhere on the board
I2C4_SDA: J2.5, J8.5, R67.2; also elsewhere on the board
NRST: J7.4; also elsewhere on the board
unnamed: D7.2 (A), J11.3, Q1.3 (D)
unnamed: D7.1 (K), J11.2, R50.1
unnamed: J1.A5 (CC1), R47.1
unnamed: J1.B5 (CC2), R45.1
unnamed: J2.2, R33.1
unnamed: J2.3, R34.1
unnamed: J4.2, R35.1
unnamed: J4.3, R36.1
unnamed: J4.4, R37.1
unnamed: J4.5, R38.1
unnamed: J5.2, R39.1
unnamed: J5.3, R40.1
unnamed: J5.4, R41.1
unnamed: J5.5, R42.1
unnamed: J8.2, R51.1
unnamed: J8.3, R52.1
unnamed: J9.3, R54.1
unnamed: J9.4, R55.1
unnamed: J12.1, R56.1
unnamed: J12.2, R57.1
unnamed: J14.2, R58.1
unnamed: J14.3, R59.1
unnamed: J14.4, R60.1
unnamed: J14.5, R61.1
unnamed: J15.2, R62.1
unnamed: J16.3, R63.1
unnamed: J16.4, R64.1
unnamed: J17.2, R66.1
unnamed: J17.3, R67.1
unnamed: C62.2, J19.1, R68.2
unnamed: C63.2, J20.1, R69.2
unnamed: C64.2, J21.1, R70.2
unnamed: C65.2, J22.1, R71.2
unnamed: C70.2, J23.1, R72.2
unnamed: C71.2, J24.1, R73.2
unnamed: C72.2, J25.1, R74.2
unnamed: C73.2, J26.1, R75.2
unnamed: C80.2, J27.1, R76.2
unnamed: C81.2, J28.1, R77.2
unnamed: C82.2, J29.1, R78.2
unnamed: C83.2, J30.1, R79.2
unnamed: C89.2, J31.1, R80.2
unnamed: C90.2, J32.1, R81.2
unnamed: C91.2, J33.1, R82.2
unnamed: C92.2, J34.1, R83.2
unnamed: Q1.1 (G), R49.1, R53.2
unnamed: R84.1, U16.5 (ILIM)
unnamed: R85.1, U17.5 (ILIM)
unnamed: R86.1, U18.5 (ILIM)
unnamed: R87.1, U19.5 (ILIM)
unnamed: R88.1, U20.5 (ILIM)
unnamed: R89.1, U21.5 (ILIM)
unnamed: R90.1, U22.5 (ILIM)
unnamed: R91.1, U23.5 (ILIM)
unnamed: R92.1, U24.5 (ILIM)
unnamed: R102.1, U25.5 (ILIM)
SAFETY_IN: J15.3, R65.2; also elsewhere on the board
SD_CLK: J10.5 (CLK); also elsewhere on the board
SD_CMD: J10.3 (CMD), R44.2; also elsewhere on the board
SD_DAT0: J10.7 (DAT0), R43.2; also elsewhere on the board
SD_DAT1: J10.8 (DAT1), R32.2; also elsewhere on the board
SD_DAT2: J10.1 (DAT2), R48.2; also elsewhere on the board
SD_DAT3: J10.2 (DAT3/CD), R46.2; also elsewhere on the board
SD_DET: J10.9 (DET); also elsewhere on the board
SPI5_MISO: J3.3; also elsewhere on the board
SPI5_MOSI: J3.4; also elsewhere on the board
SPI5_SCK: J3.2; also elsewhere on the board
SWCLK: J7.2; also elsewhere on the board
SWDIO: J7.3; also elsewhere on the board
TIM1_CH1: R79.1; also elsewhere on the board
TIM1_CH2: R77.1; also elsewhere on the board
TIM1_CH3: R83.1; also elsewhere on the board
TIM2_CH1: R68.1; also elsewhere on the board
TIM2_CH2: R70.1; also elsewhere on the board
TIM2_CH3: R72.1; also elsewhere on the board
TIM3_CH2: R74.1; also elsewhere on the board
TIM3_CH3: R76.1; also elsewhere on the board
TIM3_CH4: R78.1; also elsewhere on the board
TIM4_CH2: R71.1; also elsewhere on the board
TIM4_CH3: R69.1; also elsewhere on the board
TIM5_CH1: R80.1; also elsewhere on the board
TIM5_CH2: R82.1; also elsewhere on the board
TIM8_CH1: R75.1; also elsewhere on the board
TIM8_CH2: R73.1; also elsewhere on the board
TIM8_CH4: R81.1; also elsewhere on the board
UART4_RX: R52.2; also elsewhere on the board
UART4_TX: R51.2; also elsewhere on the board
UART7_CTS: R41.2; also elsewhere on the board
UART7_RTS: R42.2; also elsewhere on the board
UART7_RX: R40.2; also elsewhere on the board
UART7_TX: R39.2; also elsewhere on the board
USART1_RX: R34.2; also elsewhere on the board
USART1_TX: R33.2; also elsewhere on the board
USART2_CTS: R37.2; also elsewhere on the board
USART2_RTS: R38.2; also elsewhere on the board
USART2_RX: R36.2; also elsewhere on the board
USART2_TX: R35.2; also elsewhere on the board
USART3_CTS: R60.2; also elsewhere on the board
USART3_RTS: R61.2; also elsewhere on the board
USART3_RX: R59.2; also elsewhere on the board
USART3_TX: R58.2; also elsewhere on the board
USART6_RX: J6.2; also elsewhere on the board
USB_D+: U15.4 (I/O2); also elsewhere on the board
USB_D-: U15.6 (I/O1); also elsewhere on the board
~CAN2_OC: R101.1, U24.4 (~FAULT); also elsewhere on the board
~CAN_OC: R98.1, U21.4 (~FAULT); also elsewhere on the board
~CS_EXT1: J3.5; also elsewhere on the board
~CS_EXT2: J3.6; also elsewhere on the board
~GPS_OC: R99.1, U22.4 (~FAULT); also elsewhere on the board
~I2C_OC: R97.1, U20.4 (~FAULT); also elsewhere on the board
~RC_OC: R103.1, U25.4 (~FAULT); also elsewhere on the board
~SAFETY_LED: R62.2; also elsewhere on the board
~SERIAL4_OC: R95.1, U18.4 (~FAULT); also elsewhere on the board
~SERIAL5_OC: R96.1, U19.4 (~FAULT); also elsewhere on the board
~SPI_OC: R100.1, U23.4 (~FAULT); also elsewhere on the board
~TELEM1_OC: R93.1, U16.4 (~FAULT); also elsewhere on the board
~TELEM2_OC: R94.1, U17.4 (~FAULT); also elsewhere on the board

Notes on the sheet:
MOUNTING HOLES
IMAX = 616mA
PERIPHERALS
SD CARD
USB
